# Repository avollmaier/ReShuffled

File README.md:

## Informatik-Konzept
Den informatischen Teil der Arbeit kann man grundsätzlich in 2 Bereiche aufteilen. Es soll
eine einfache grafische Benutzeroberfläche gestaltet werden, auf welcher man den Mischvorgang
steuern sowie grundlegende Einstellungen des Spieles vornehmen kann. Aus programmtechnischen
Gründen wird hierfür die Programmiersprache Java und das GUI-Toolkit Swing verwendet.
Die Hardwarekomponenten setzen sich aus einem Raspberry Pi 3B+ und einem 7"LCD Touchscreen
der Firma Elecrow zusammen.

Zusätzlich besteht dieser Teilbereich der Arbeit auch aus der hardwarenahen Programmierung der
Hauptplatine. Mithilfe der Programmiersprache C sollte der verbaute 8-Bit Mikrocontroller der
AVR-Familie namens ATmega324P programmiert werden. Dieser steuert den gesamten Ablauf
der Maschiene.
Der Datenaustausch zwischen der Hauptplatine und dem Raspberry PI erfolgt über die serielle
Schnittstelle namens UART. Im Hintergrund wird gleichzeitig eine Json Logdatei geschrieben.
## Installation
TODO

# Dokumentation
## Wichtigste Funktionen
### Raspberry

 - Steuerung der gesamten Maschine
 - Grafische Benutzeroberfläche
 - Übertragung der Daten per UART  
 - Auswertung der Daten

### Motherboard
 * Einlesen der Sensordaten  
 * Übertragung der Daten per UART  
 * Auswertung der Daten
 * Steuerung des Motors sowie der Hubmagnete
## Arten von Daten und deren Erfassung
  
 * 3x Kapazitiver Sensor (DIGITAL)

## Protokoll
Das Protokoll ist verbindungslos und Request-Response- (Master-Slave) -orientiert. Die Datenübertragung erfolgt textuell wobei nur Großbuchstaben verwendet werden dürfen, die CRC32-Prüfsumme wird mit einer im Raspberry gespeicherte Tabelle realisiert und nur über die Daten und dem Trennzeichen `#` berechnet. 

### Aufbau:
| Doppelpunkt `:` | Daten (ASCII)| Trennzeichen `#` | CRC32-Prüfsumme | Semicolon `\n` |
| --------------- | ------------------------------------------------ | ----------- | --------------- | ------------- |
| 8-Bit | 16-Bit | 8-Bit | 32-Bit | 8-Bit

### Requests (mit Response-Beispielen)
| Request | Request-String Rx | Response | Response-String Tx |
| ------- | ------------- | -------- | ------------------ |
| INIT | `IN` | Initialisierungs-Zustand | `:OK#CRC;` oder`:E<code>#CRC;` |
| SHUFFLE | `SH` | setzt State "Shuffle" | `:OK#CRC;` oder`:E<code>#CRC;` |
| DEAL | `D<Anzahl der karten>` | setzt State "Deal" | `:OK#CRC;` oder`:E<code>#CRC;` 
| AUTODEAL | `A<Anzahl der karten>` | setzt State "AutoDeal" (standartmäßig 4x5) | `:OK#CRC;` oder`:E<code>#CRC;` |
| SHUTDOWN | `XX` | setzt State "Shutdown" | `:OK#CRC;` oder`:E<code>#CRC;` |

### Requests (mit Response-Beispielen)
Als Response kann entweder `:OK#CRC;` als Zeichen für ein gültiges Verarbeiten des Befehls am Mainboard oder ein `:E<code>#CRC;` zurückgegeben werden.  Dieser Errorcode sagt folgendes aus:

 - `:E<1>#CRC;` -->  TODO
 - `:E<2>#CRC;` -->  TODO
 - `:E<3>#CRC;` -->  TODO

# CommLog-Files
  Im Entwicklunsmodus die gesamte Kommunikation als .json-Datei in das Verzeichnis `/home/pi/ReShuffled_PI/reshuffled.log` gespeichert.
  
  Diese Datei ist so zu lesen:  
### REQUESTS
`Zeitstempel : Name des Requests`
### RESPONSES
`Zeitstempel : Response CRC: *empfangener CRC* <-> *berechneter CRC*`

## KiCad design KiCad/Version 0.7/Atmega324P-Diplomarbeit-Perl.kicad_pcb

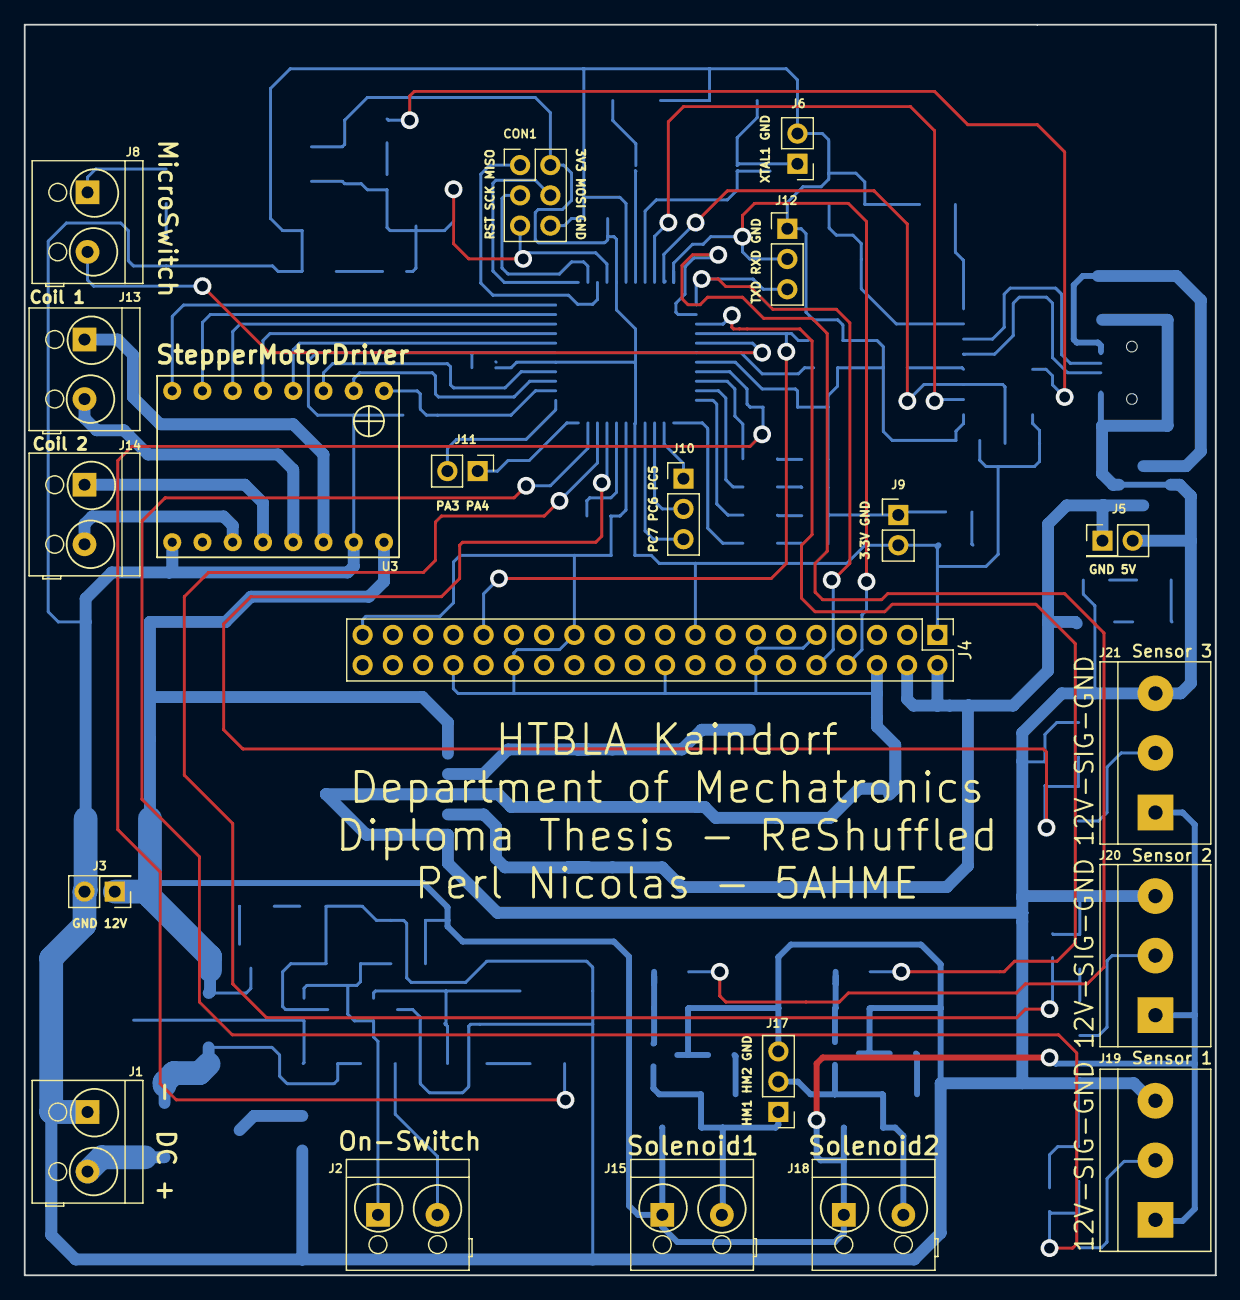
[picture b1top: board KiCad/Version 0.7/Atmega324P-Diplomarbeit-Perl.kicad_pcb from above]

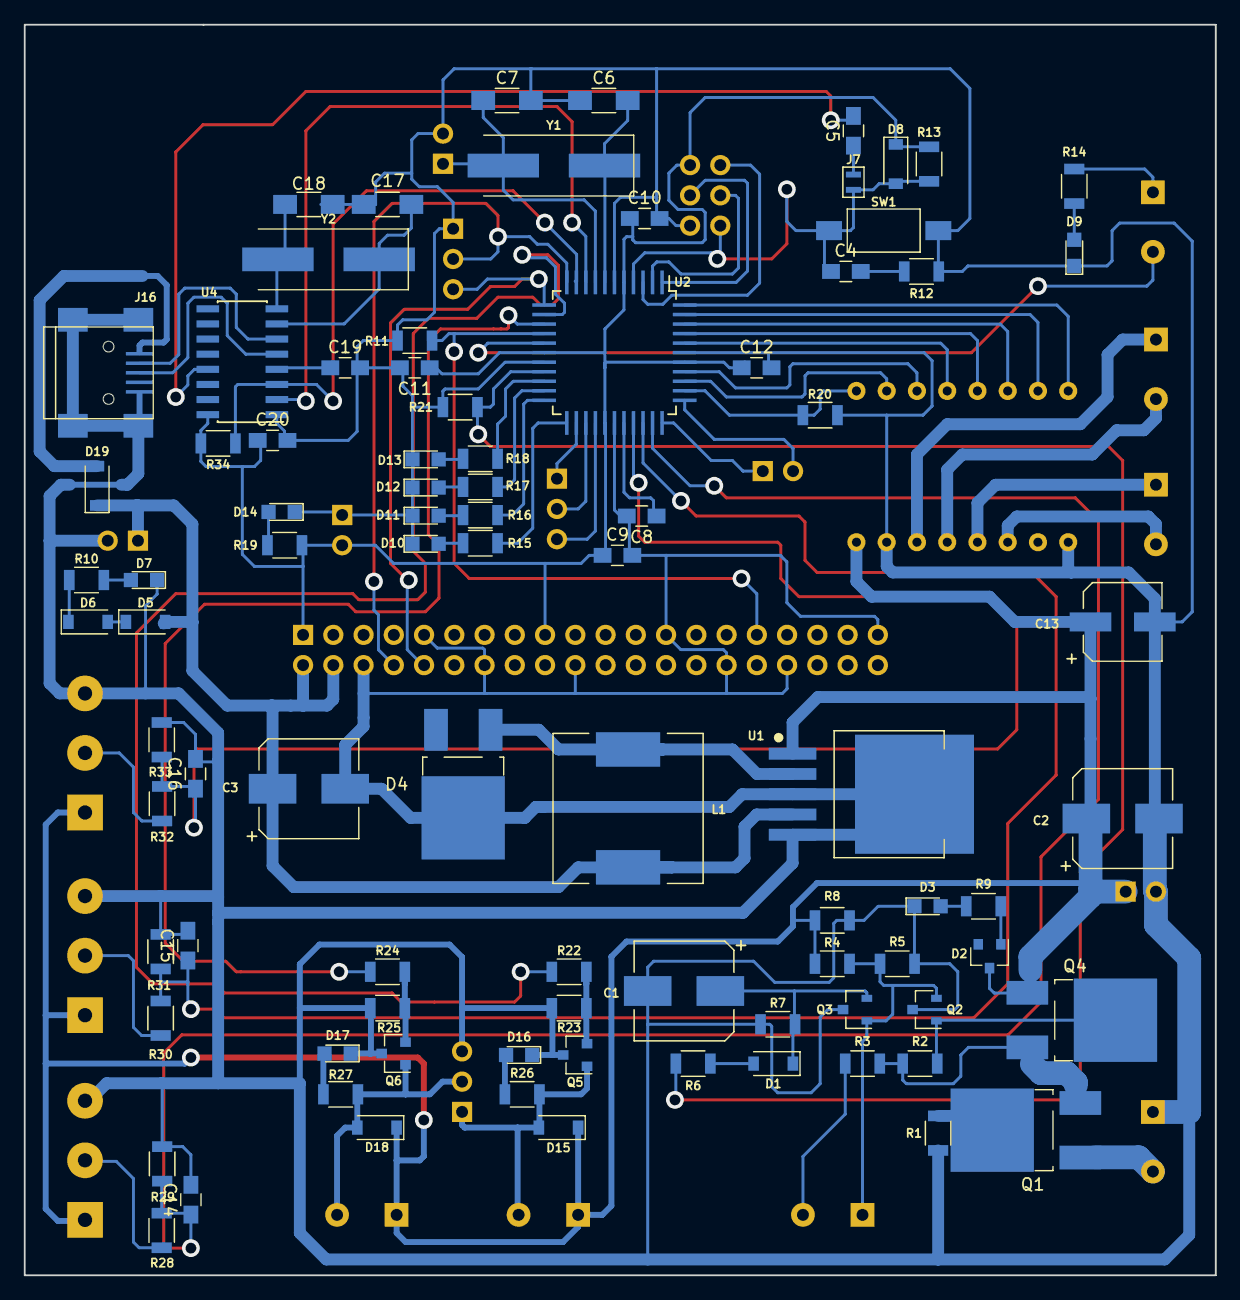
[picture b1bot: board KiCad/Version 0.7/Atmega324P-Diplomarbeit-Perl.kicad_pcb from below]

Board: 2 copper layers, 100.0 x 105.0 mm, 109 parts (88 on the bottom side), 82 nets.

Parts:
C1, C2: 100µ; CP_Elec_8x6.7
C3: 1000µ; CP_Elec_8x6.7
C4, C5, C8, C9, C10, C11, C12, C14, C15, C16, C19, C20: 100n; C_0805_HandSoldering
C6, C7, C17, C18: 22pF; C_1206_HandSoldering
C13: 47µ; CP_Elec_6.3x5.8
CON1: AVR-ISP-6; Pin_Header_Straight_2x03_Pitch2.54mm
D1, D8, D19: MBR130; D_SOD-123
D2: BZX84-C8V2; D_SOT-23_ANK
D3, D7, D9, D10, D11, D12, D13, D14, D16, D17: LED; LED_0805
D4: MBRD340; TO-252-2_Rectifier
D5, D6, D15, D18: RR264M; D_SOD-123
J1: Input_12V; Terminalblock-2x-5mm
J2: PowerOn_Button; Terminalblock-2x-5mm
J3, J5: Conn_01x02; Pin_Header_Straight_2x01_Pitch2.54mm
J4: Raspberry_Pi_3B+; Pin_Header_Straight_2x20_Pitch2.54mm
J6, J9, J11: Conn_01x02; Pin_Header_Straight_1x02_Pitch2.54mm
J7: GS2
J8: Microswitch; Terminalblock-2x-5mm
J10, J12, J17: Conn_01x03; Pin_Header_Straight_1x03_Pitch2.54mm
J13: Stepper1; Terminalblock-2x-5mm
J14: Stepper2; Terminalblock-2x-5mm
J15: Solenoid1; Terminalblock-2x-5mm
J16: USB_OTG; USB_Mini-B
J18: Solenoid2; Terminalblock-2x-5mm
J19: Cap_Sensor1; Terminalblock-3x-5mm
J20: Cap_Sensor2; Terminalblock-3x-5mm
J21: Cap_Sensor3; Terminalblock-3x-5mm
L1: 100µ; L_12x12mm_h6mm
Q1, Q4: FDD6637; TO-252-2_Rectifier
Q2, Q3, Q5, Q6: FDN337N; SOT-23
R1, R8, R11, R13, R20, R21, R34: 47k; R_1206
R2, R3, R4, R5, R23, R25: 10k; R_1206
R6, R9, R10, R12, R14, R15, R16, R17, R18, R19, R22, R24, R26, R27: 560; R_1206
R7: 100k; R_1206
R28, R30, R32: 5.6k; R_1206
R29, R31, R33: 4.7k; R_1206
SW1: SW_Push; SW_SPST_FSMSM
U1: LM2576-5.0WU; DPAK6P170_1524X459L254X81N
U2: ATMEGA324P-20AU; TQFP-44_10x10mm_Pitch0.8mm_Handsolded
U3: StepperMotorDriver; StepperSocket
U4: CH340G; SOIC-16_3.9x9.9mm_Pitch1.27mm_HANDSOLDERED
Y1: Crystal_10Mhz; Crystal_SMD_HC49-SD
Y2: Crystal_12Mhz; Crystal_SMD_HC49-SD

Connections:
12V: C2.1, C13.1, D2.1, D15.1, D18.1, J3.1, J15.1, J18.1, J19.1, J20.1, J21.1, Q4.1, R4.2, R8.1, U1.1, U3.9
+3V3: C9.1, C10.1, C11.1, C12.1, C20.1, CON1.2, D8.1, J4.1, J4.17, J9.2, R13.1, R19.1, R34.1, U2.5, U2.17, U2.27, U2.38, U4.16
+5V: C3.1, D5.2, D19.1, J4.2, J4.4, J5.1, L1.2, U1.4
/Peripherie/WATCHDOG: J4.31, R11.1, U2.15
/Peripherie/µC_RxD: J4.8, J12.2, U2.11
/Peripherie/µC_TxD: J4.10, J12.3, U2.12
DIR: U2.44, U3.8
DTR_USB: C5.2, U4.13
EN: R20.1, U2.35, U3.1
GND: C1.2, C2.2, C3.2, C6.2, C7.2, C8.2, C9.2, C10.2, C11.2, C12.2, C13.2, C14.2, C15.2, C16.2, C17.2, C18.2, C19.2, C20.2, CON1.6, D3.1, D4.2, D7.1, D9.1, D10.1, D11.1, D12.1, D13.1, D14.1, D16.1, D17.1, J1.1, J3.2, J4.6, J4.9, J4.14, J4.20, J4.25, J4.30, J4.34, J4.39, J5.2, J6.2, J9.1, J12.1, J16.5, J16.6, J17.3, J19.3, J20.3, J21.3, Q2.3, Q3.3, Q5.3, Q6.3, R1.1, R5.2, R7.2, R8.2, R11.2, R12.1, R20.2, R21.2, R23.2, R25.2, R29.2, R31.2, R33.2, SW1.1, U1.3, U1.5, U1.6, U2.6, U2.18, U2.28, U2.39, U3.10, U3.16, U4.1
HM1: R22.2, U2.13
HM2: R24.2, U2.14
LED1: R18.2, U2.20
LED2: R17.2, U2.21
LED3: R16.2, U2.22
LED4: R15.2, U2.23
M0: U2.36, U3.2
M1: U2.37, U3.3
M2: U2.40, U3.4
MISO: CON1.1, U2.3
MOSI: CON1.4, U2.1
MSWITCH: J8.2, U2.16
unnamed: C1.1, D1.1, Q3.2, R7.1
unnamed: C4.2, R12.2
unnamed: C5.1, J7.2
unnamed: C6.1, U2.7, Y1.1
unnamed: C7.1, J6.1, U2.8, Y1.2
unnamed: C8.1, U2.29
unnamed: C17.1, U4.7, Y2.1
unnamed: C18.1, U4.8, Y2.2
unnamed: C19.1, U4.4
unnamed: D1.2, R6.1
unnamed: D2.2, R9.1
unnamed: D3.2, R9.2
unnamed: D4.1, L1.1, U1.2
unnamed: D5.1, D6.2
unnamed: D6.1, R10.1
unnamed: D7.2, R10.2
unnamed: D9.2, R14.1
unnamed: D10.2, R15.1
unnamed: D11.2, R16.1
unnamed: D12.2, R17.1
unnamed: D13.2, R18.1
unnamed: D14.2, R19.2
unnamed: D15.2, J15.2, J17.1, Q5.1, R26.2
unnamed: D16.2, R26.1
unnamed: D17.2, R27.1
unnamed: D18.2, J17.2, J18.2, Q6.1, R27.2
unnamed: D19.2, J16.1
unnamed: J1.2, Q1.1
unnamed: J2.1, Q2.2, Q3.1, R4.1, R5.1
unnamed: J2.2, R3.2
unnamed: J8.1, R14.2
unnamed: J10.1, U2.24
unnamed: J10.2, U2.25
unnamed: J10.3, U2.26
unnamed: J11.1, U2.33
unnamed: J11.2, U2.34
unnamed: J13.1, U3.11
unnamed: J13.2, U3.12
unnamed: J14.1, U3.13
unnamed: J16.2, U4.6
unnamed: J16.3, U4.5
unnamed: J19.2, R28.1
unnamed: J20.2, R30.1
unnamed: J21.2, R32.1
unnamed: Q1.2, R1.2
unnamed: Q1.3, Q4.3, R2.1, R3.1
unnamed: Q2.1, Q4.2, R2.2
unnamed: Q5.2, R22.1, R23.1
unnamed: Q6.2, R24.1, R25.1
RESET_M: U2.41, U3.5
RST: C4.1, CON1.5, D8.2, J7.1, R13.2, SW1.2, U2.4
RxD_USB: R34.2, U2.10, U4.3
S1: C14.1, R28.2, R29.1, U2.32
S2: C15.1, R30.2, R31.1, U2.31
S3: C16.1, R32.2, R33.1, U2.30
SCK: CON1.3, U2.2
SLEEP: U2.42, U3.6
STEP: U2.43, U3.7
TxD_USB: U2.9, U4.2
UNLATCH: R6.2, R21.1, U2.19

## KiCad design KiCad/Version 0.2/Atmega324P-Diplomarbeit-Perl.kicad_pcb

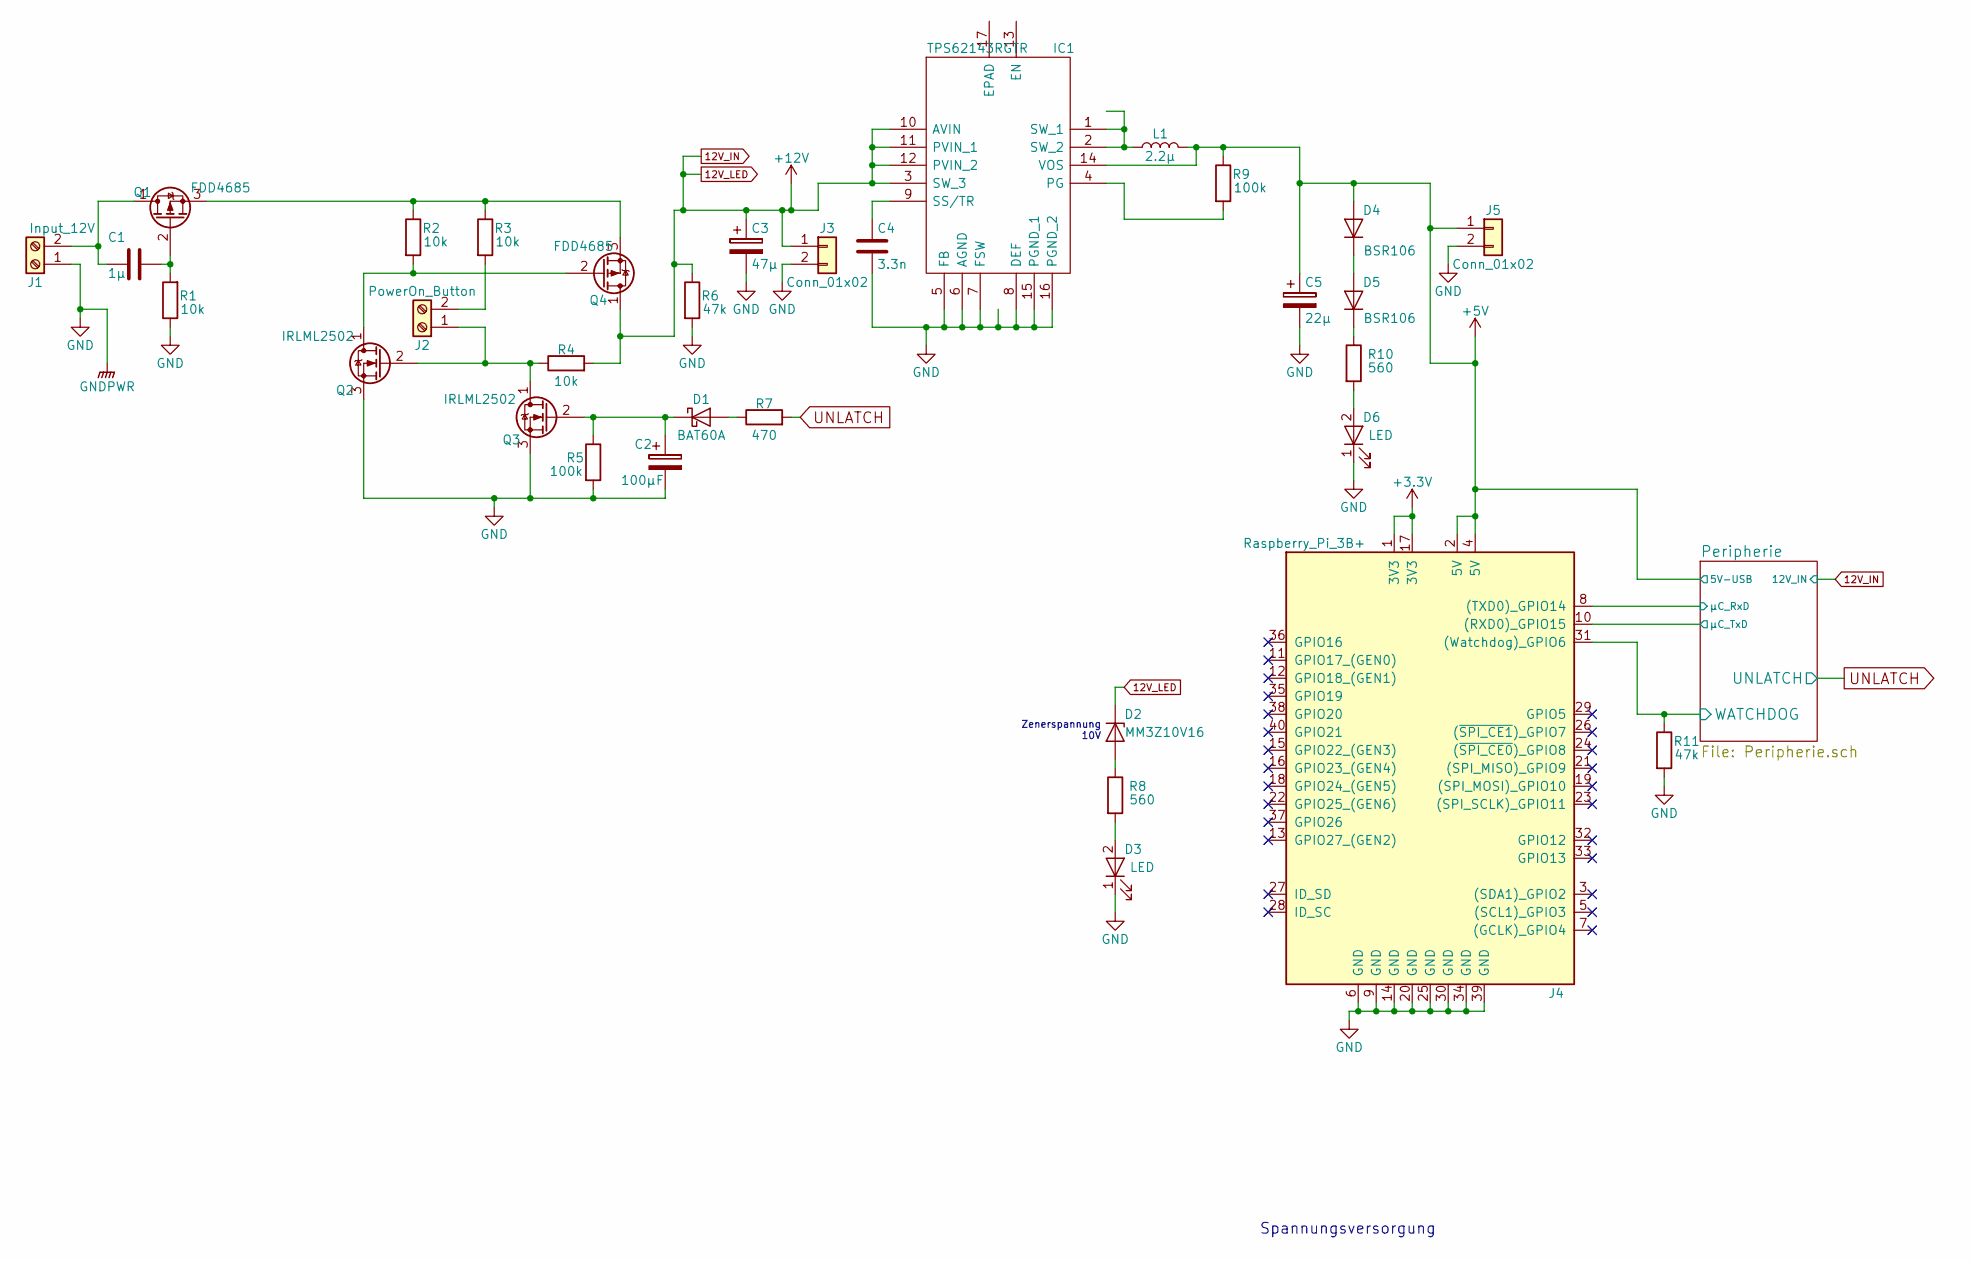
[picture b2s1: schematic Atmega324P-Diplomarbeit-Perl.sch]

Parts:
C1: 1µ; CP_Elec_4x5.3
C2: 100µF; CP_Elec_6.3x7.7
C3: 47µ; CP_Elec_6.3x7.7
C4: 3.3n; C_1206_HandSoldering
C5: 22µ; CP_Elec_6.3x7.7
D1: BAT60A; D_SOD-323
D2: MM3Z10V16; D_SOD-323
D3, D6: LED; D_0805
D4, D5: BSR106; D_SOD-323
IC1: TPS62143RGTR; QFN50P300X300X100-17N-D; Mouser Part Number 595-TPS62143RGTR
J1: Input_12V; Terminalblock-2x-5mm
J2: PowerOn_Button; Terminalblock-2x-5mm
J3, J5: Conn_01x02; Pin_Header_Straight_2x01_Pitch2.54mm
J4: Raspberry_Pi_3B+; Pin_Header_Straight_2x20
L1: 2.2µ; L_Wuerth_MAPI-4020
Q1, Q4: FDD4685; TO-252-3_TabPin2
Q2, Q3: IRLML2502; SOT-23
R1, R2, R3, R4: 10k; R_1206
R5, R9: 100k; R_1206
R6, R11: 47k; R_1206
R7: 470; R_1206
R8, R10: 560; R_1206

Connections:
+3V3: J4.1 (3V3), J4.17 (3V3); also elsewhere on the board
+5V: C5.1, D4.2 (A), IC1.14 (VOS), J4.2 (5V), J4.4 (5V), J5.1, L1.2, R9.1; also elsewhere on the board
/Peripherie/WATCHDOG: J4.31 ((Watchdog)_GPIO6), R11.1; also elsewhere on the board
/Peripherie/µC_RxD: J4.8 ((TXD0)_GPIO14); also elsewhere on the board
/Peripherie/µC_TxD: J4.10 ((RXD0)_GPIO15); also elsewhere on the board
GND: C2.2, C3.2, C4.2, C5.2, D3.1 (K), D6.1 (K), IC1.5 (FB), IC1.6 (AGND), IC1.7 (FSW), IC1.8 (DEF), IC1.15 (PGND_1), IC1.16 (PGND_2), IC1.17 (EPAD), J1.1, J3.2, J4.6 (GND), J4.9 (GND), J4.14 (GND), J4.20 (GND), J4.25 (GND), J4.30 (GND), J4.34 (GND), J4.39 (GND), J5.2, Q2.3 (S), Q3.3 (S), R1.1, R5.2, R6.2, R11.2; also elsewhere on the board
unnamed: C1.1, Q1.2 (G), R1.2
unnamed: C1.2, J1.2, Q1.1 (D)
unnamed: C2.1, D1.1 (K), Q3.2 (G), R5.1
unnamed: C4.1, IC1.9 (SS/TR)
unnamed: D1.2 (A), R7.1
unnamed: D2.2 (A), R8.1
unnamed: D3.2 (A), R8.2
unnamed: D4.1 (K), D5.2 (A)
unnamed: D5.1 (K), R10.1
unnamed: D6.2 (A), R10.2
unnamed: IC1.4 (PG), R9.2
unnamed: J2.1, Q2.2 (G), Q3.1 (D), R4.1
unnamed: J2.2, R3.2
unnamed: Q1.3 (S), Q4.3 (S), R2.1, R3.1
unnamed: Q2.1 (D), Q4.2 (G), R2.2
UNLATCH: R7.2; also elsewhere on the board

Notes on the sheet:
Spannungsversorgung
Zenerspannung 10V

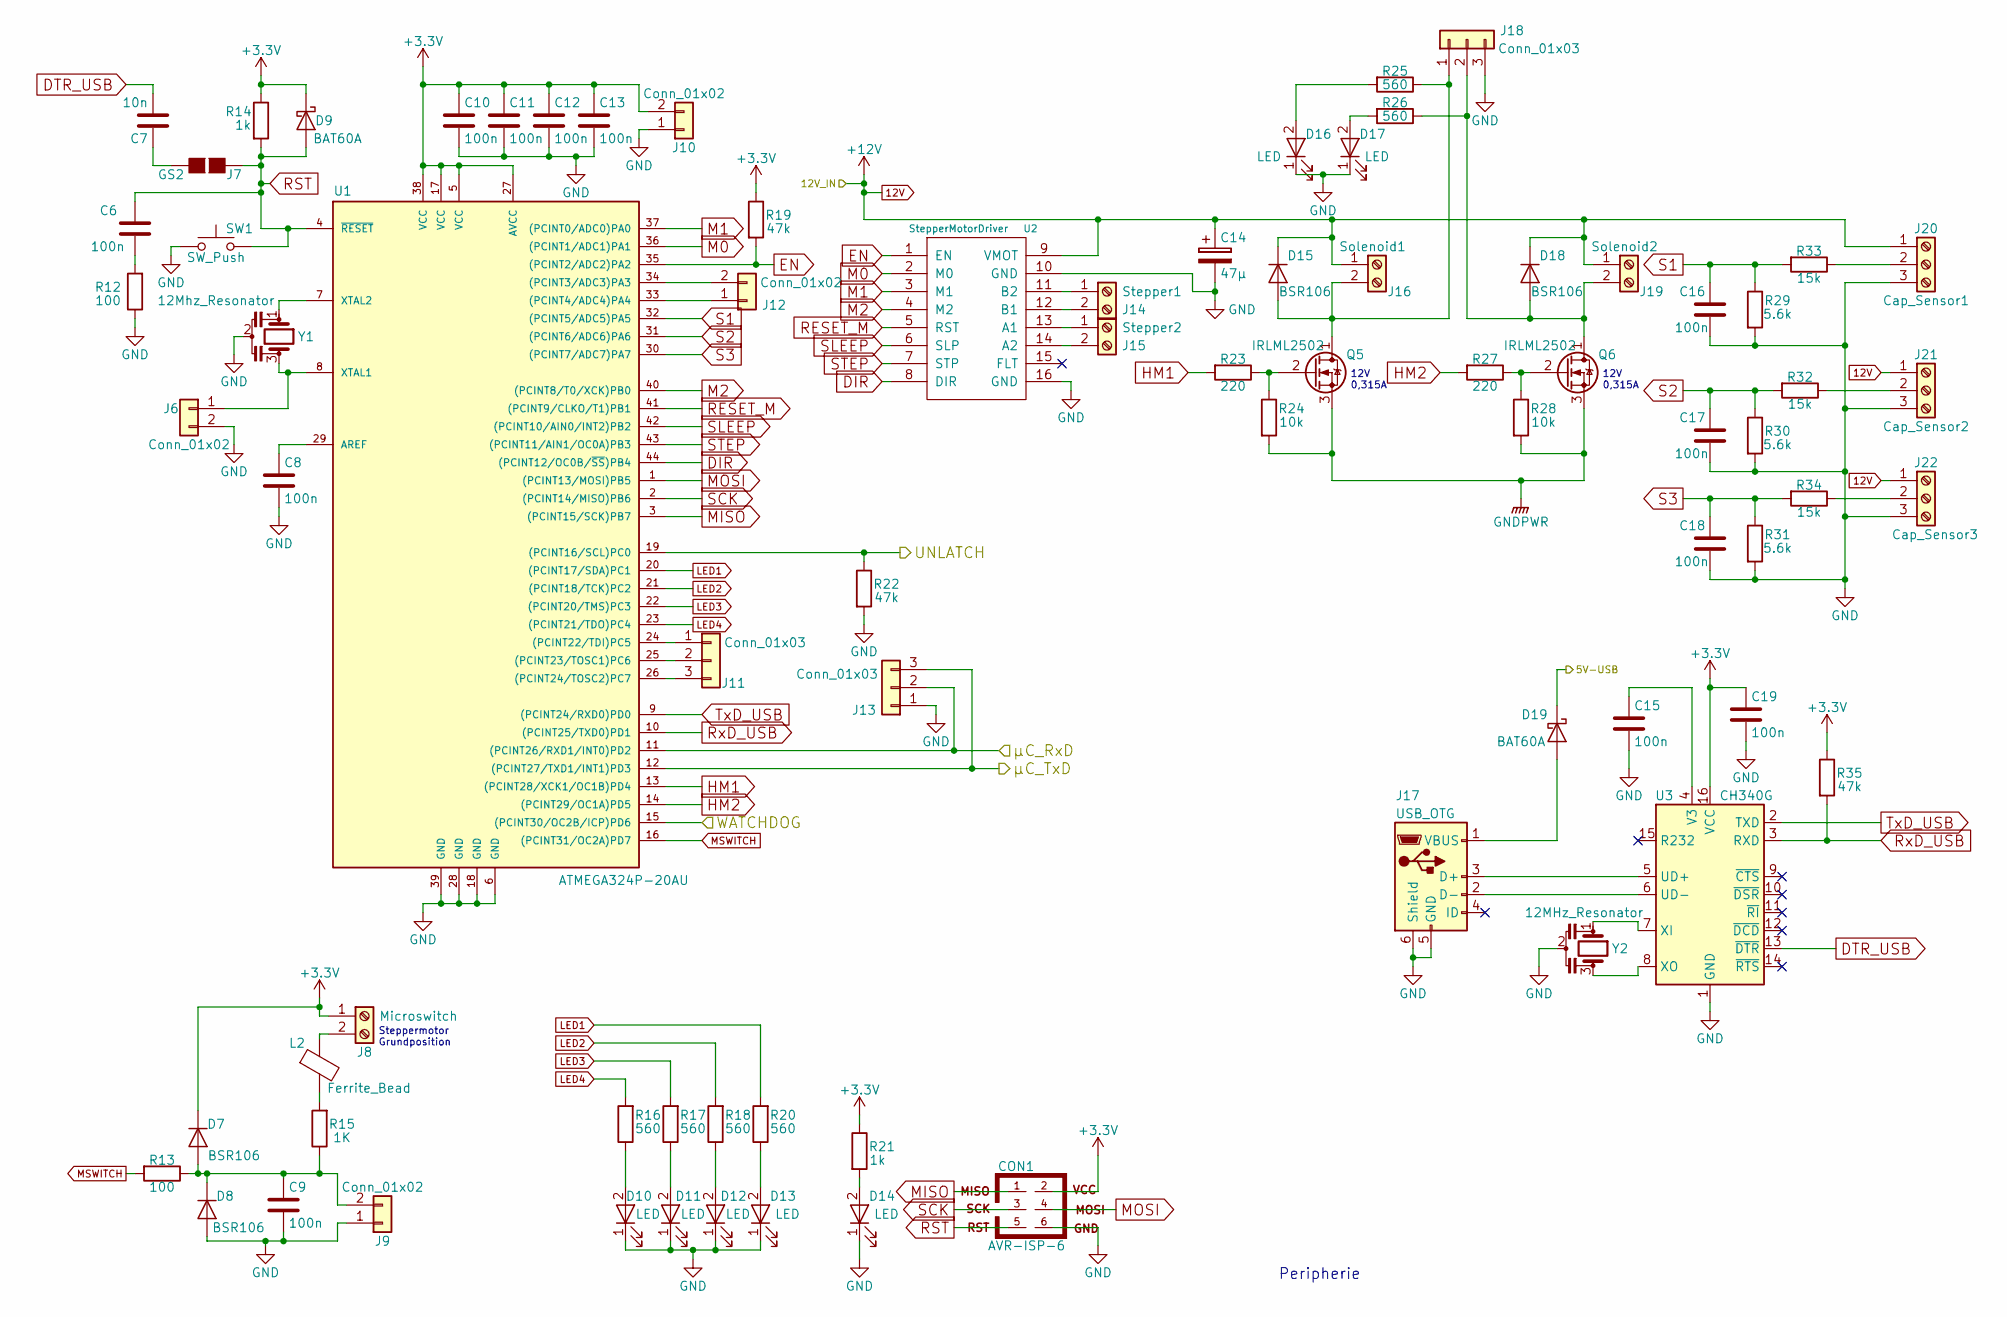
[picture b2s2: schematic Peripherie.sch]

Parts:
C6, C8, C9, C10, C11, C12, C13, C15, C16, C17, C18, C19: 100n; C_1206_HandSoldering
C7: 10n; C_1206_HandSoldering
C14: 47µ; CP_Elec_6.3x7.7
CON1: AVR-ISP-6; Pin_Header_Straight_2x03_Pitch2.54mm
D7, D8, D15, D18: BSR106; D_SOD-323
D9, D19: BAT60A; D_SOD-323
D10, D11, D12, D13, D14, D16, D17: LED; D_0805
J6, J9, J10, J12: Conn_01x02; Pin_Header_Straight_1x02_Pitch2.54mm
J7: GS2
J8: Microswitch; Terminalblock-2x-5mm
J11, J13, J18: Conn_01x03; Pin_Header_Straight_1x03_Pitch2.54mm
J14: Stepper1; Terminalblock-2x-5mm
J15: Stepper2; Terminalblock-2x-5mm
J16: Solenoid1; Terminalblock-2x-5mm
J17: USB_OTG; USB_Mini-B-THT
J19: Solenoid2; Terminalblock-2x-5mm
J20: Cap_Sensor1; Terminalblock-3x-5mm
J21: Cap_Sensor2; Terminalblock-3x-5mm
J22: Cap_Sensor3; Terminalblock-3x-5mm
L2: Ferrite_Bead; L_0805_HandSoldering
Q5, Q6: IRLML2502; SOT-23
R12, R13: 100; R_1206
R14, R21: 1k; R_1206
R15: 1K; R_1206
R16, R17, R18, R20, R25, R26: 560; R_1206
R19, R22, R35: 47k; R_1206
R23, R27: 220; R_1206
R24, R28: 10k; R_1206
R29, R30, R31: 5.6k; R_1206
R32, R33, R34: 15k; R_1206
SW1: SW_Push; SW_SPST_FSMSM
U1: ATMEGA324P-20AU; TQFP-44_10x10mm_Pitch0.8mm_Handsolded
U2: StepperMotorDriver; StepperSocket
U3: CH340G; SOIC-16_3.9x9.9mm_Pitch1.27mm_HANDSOLDERED
Y1: 12Mhz_Resonator; Resonator-3pin_w7.0mm_h2.5mm
Y2: 12MHz_Resonator; Resonator-3pin_w7.0mm_h2.5mm

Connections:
+3V3: C10.1, C11.1, C12.1, C13.1, C19.1, CON1.2, D7.1 (K), D9.1 (K), J8.1, J10.2, R14.1, R19.1, R21.1, R35.1, U1.5 (VCC), U1.17 (VCC), U1.27 (AVCC), U1.38 (VCC), U3.16 (VCC); also elsewhere on the board
+5V: D19.1 (K); also elsewhere on the board
/Peripherie/WATCHDOG: U1.15 ((PCINT30/OC2B/ICP)PD6); also elsewhere on the board
/Peripherie/µC_RxD: J13.2, U1.11 ((PCINT26/RXD1/INT0)PD2); also elsewhere on the board
/Peripherie/µC_TxD: J13.3, U1.12 ((PCINT27/TXD1/INT1)PD3); also elsewhere on the board
DIR: U1.44 ((PCINT12/OC0B/~SS~)PB4), U2.8 (DIR)
DTR_USB: C7.2, U3.13 (~DTR)
EN: R19.2, U1.35 ((PCINT2/ADC2)PA2), U2.1 (EN)
GND: C8.2, C9.2, C10.2, C11.2, C12.2, C13.2, C14.2, C15.2, C16.2, C17.2, C18.2, C19.2, CON1.6, D8.2 (A), D10.1 (K), D11.1 (K), D12.1 (K), D13.1 (K), D14.1 (K), D16.1 (K), D17.1 (K), J6.2, J9.1, J10.1, J13.1, J17.5 (GND), J17.6 (Shield), J18.3, J20.3, J21.3, J22.3, Q5.3 (S), Q6.3 (S), R12.1, R22.2, R24.2, R28.2, R29.2, R30.2, R31.2, SW1.1, U1.6 (GND), U1.18 (GND), U1.28 (GND), U1.39 (GND), U2.10 (GND), U2.16 (GND), U3.1 (GND), Y1.2, Y2.2; also elsewhere on the board
HM1: R23.2, U1.13 ((PCINT28/XCK1/OC1B)PD4)
HM2: R27.2, U1.14 ((PCINT29/OC1A)PD5)
LED1: R20.2, U1.20 ((PCINT17/SDA)PC1)
LED2: R18.2, U1.21 ((PCINT18/TCK)PC2)
LED3: R17.2, U1.22 ((PCINT20/TMS)PC3)
LED4: R16.2, U1.23 ((PCINT21/TDO)PC4)
M0: U1.36 ((PCINT1/ADC1)PA1), U2.2 (M0)
M1: U1.37 ((PCINT0/ADC0)PA0), U2.3 (M1)
M2: U1.40 ((PCINT8/T0/XCK)PB0), U2.4 (M2)
MISO: CON1.1, U1.3 ((PCINT15/SCK)PB7)
MOSI: CON1.4, U1.1 ((PCINT13/MOSI)PB5)
MSWITCH: R13.2, U1.16 ((PCINT31/OC2A)PD7)
unnamed: C6.2, R12.2
unnamed: C7.1, J7.2 (G2)
unnamed: C8.1, U1.29 (AREF)
unnamed: C9.1, D7.2 (A), D8.1 (K), J9.2, R13.1, R15.1
unnamed: C15.1, U3.4 (V3)
unnamed: D10.2 (A), R16.1
unnamed: D11.2 (A), R17.1
unnamed: D12.2 (A), R18.1
unnamed: D13.2 (A), R20.1
unnamed: D14.2 (A), R21.2
unnamed: D15.2 (A), J16.2, J18.1, Q5.1 (D), R25.1
unnamed: D16.2 (A), R25.2
unnamed: D17.2 (A), R26.2
unnamed: D18.2 (A), J18.2, J19.2, Q6.1 (D), R26.1
unnamed: D19.2 (A), J17.1 (VBUS)
unnamed: J6.1, U1.8 (XTAL1), Y1.3
unnamed: J8.2, L2.1
unnamed: J11.1, U1.24 ((PCINT22/TDI)PC5)
unnamed: J11.2, U1.25 ((PCINT23/TOSC1)PC6)
unnamed: J11.3, U1.26 ((PCINT24/TOSC2)PC7)
unnamed: J12.1, U1.33 ((PCINT4/ADC4)PA4)
unnamed: J12.2, U1.34 ((PCINT3/ADC3)PA3)
unnamed: J14.1, U2.11 (B2)
unnamed: J14.2, U2.12 (B1)
unnamed: J15.1, U2.13 (A1)
unnamed: J15.2, U2.14 (A2)
unnamed: J17.2 (D-), U3.6 (UD-)
unnamed: J17.3 (D+), U3.5 (UD+)
unnamed: J20.2, R33.1
unnamed: J21.2, R32.1
unnamed: J22.2, R34.1
unnamed: L2.2, R15.2
unnamed: Q5.2 (G), R23.1, R24.1
unnamed: Q6.2 (G), R27.1, R28.1
unnamed: U1.7 (XTAL2), Y1.1
unnamed: U3.7 (XI), Y2.1
unnamed: U3.8 (XO), Y2.3
RESET_M: U1.41 ((PCINT9/CLKO/T1)PB1), U2.5 (RST)
RST: C6.1, CON1.5, D9.2 (A), J7.1 (G1), R14.2, SW1.2, U1.4 (~RESET)
RxD_USB: R35.2, U1.10 ((PCINT25/TXD0)PD1), U3.3 (RXD)
S1: C16.1, R29.1, R33.2, U1.32 ((PCINT5/ADC5)PA5)
S2: C17.1, R30.1, R32.2, U1.31 ((PCINT6/ADC6)PA6)
S3: C18.1, R31.1, R34.2, U1.30 ((PCINT7/ADC7)PA7)
SCK: CON1.3, U1.2 ((PCINT14/MISO)PB6)
SLEEP: U1.42 ((PCINT10/AIN0/INT2)PB2), U2.6 (SLP)
STEP: U1.43 ((PCINT11/AIN1/OC0A)PB3), U2.7 (STP)
TxD_USB: U1.9 ((PCINT24/RXD0)PD0), U3.2 (TXD)
UNLATCH: R22.1, U1.19 ((PCINT16/SCL)PC0); also elsewhere on the board

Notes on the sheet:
Peripherie
12V 0,315A
Steppermotor Grundposition

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
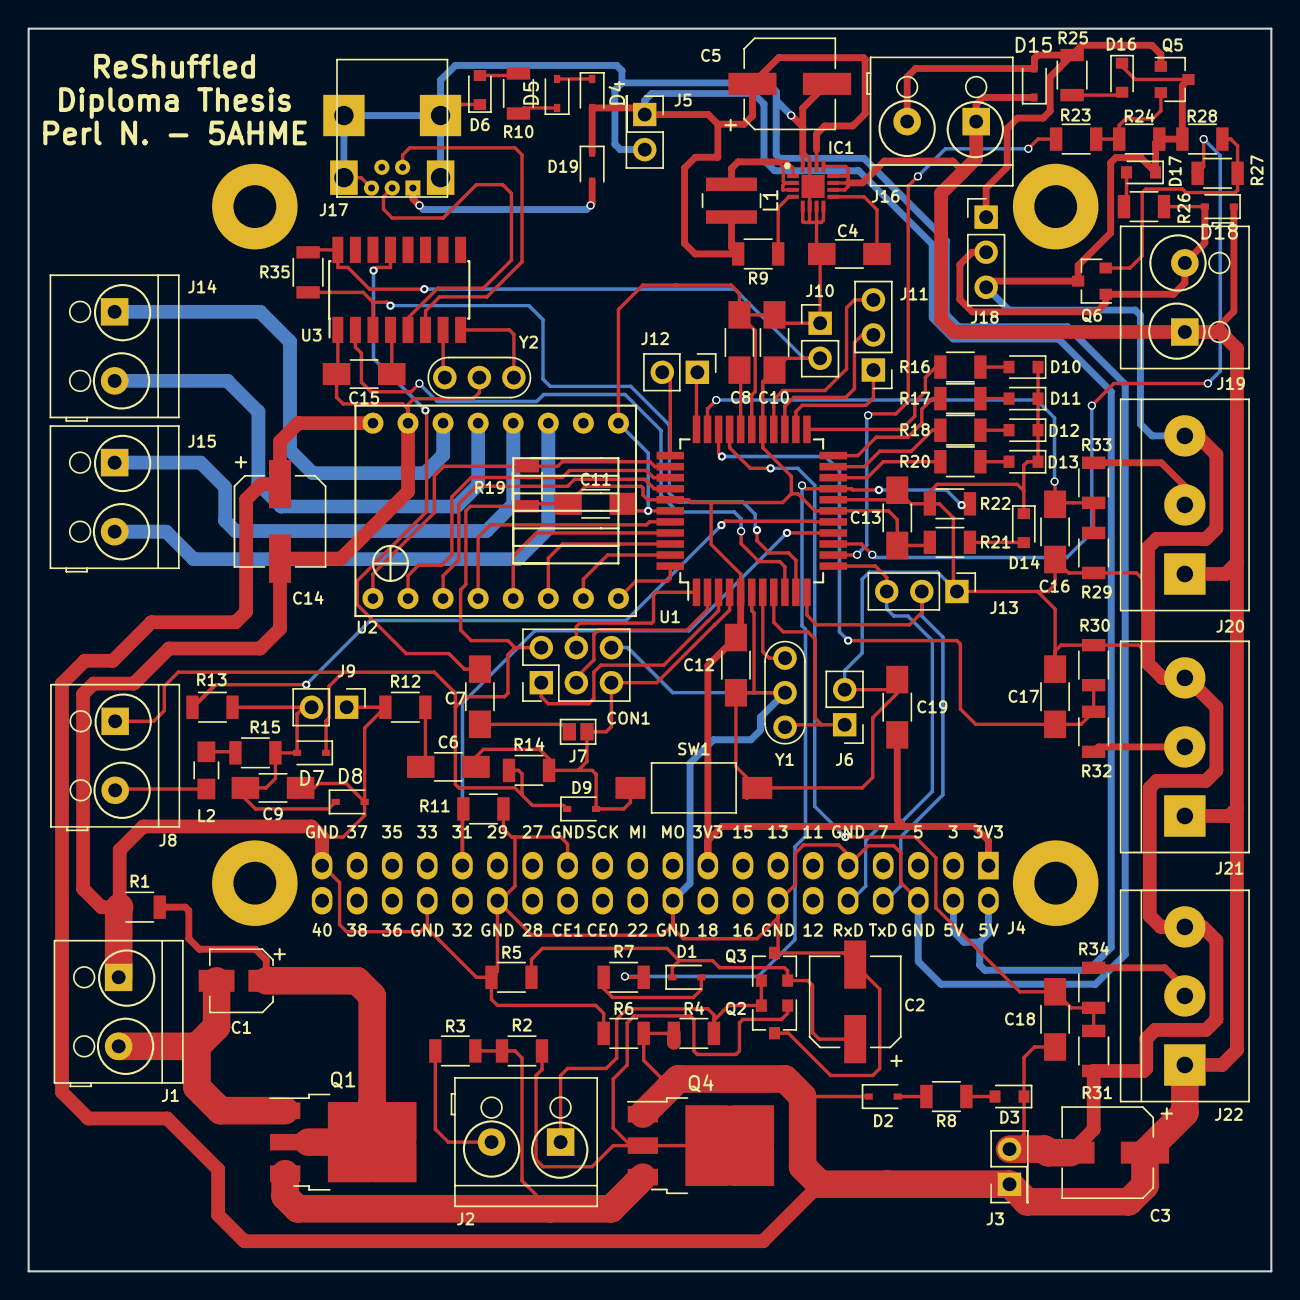
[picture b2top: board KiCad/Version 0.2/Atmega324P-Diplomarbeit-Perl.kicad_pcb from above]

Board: 2 copper layers, 90.0 x 90.0 mm, 111 parts (0 on the bottom side), 86 nets.

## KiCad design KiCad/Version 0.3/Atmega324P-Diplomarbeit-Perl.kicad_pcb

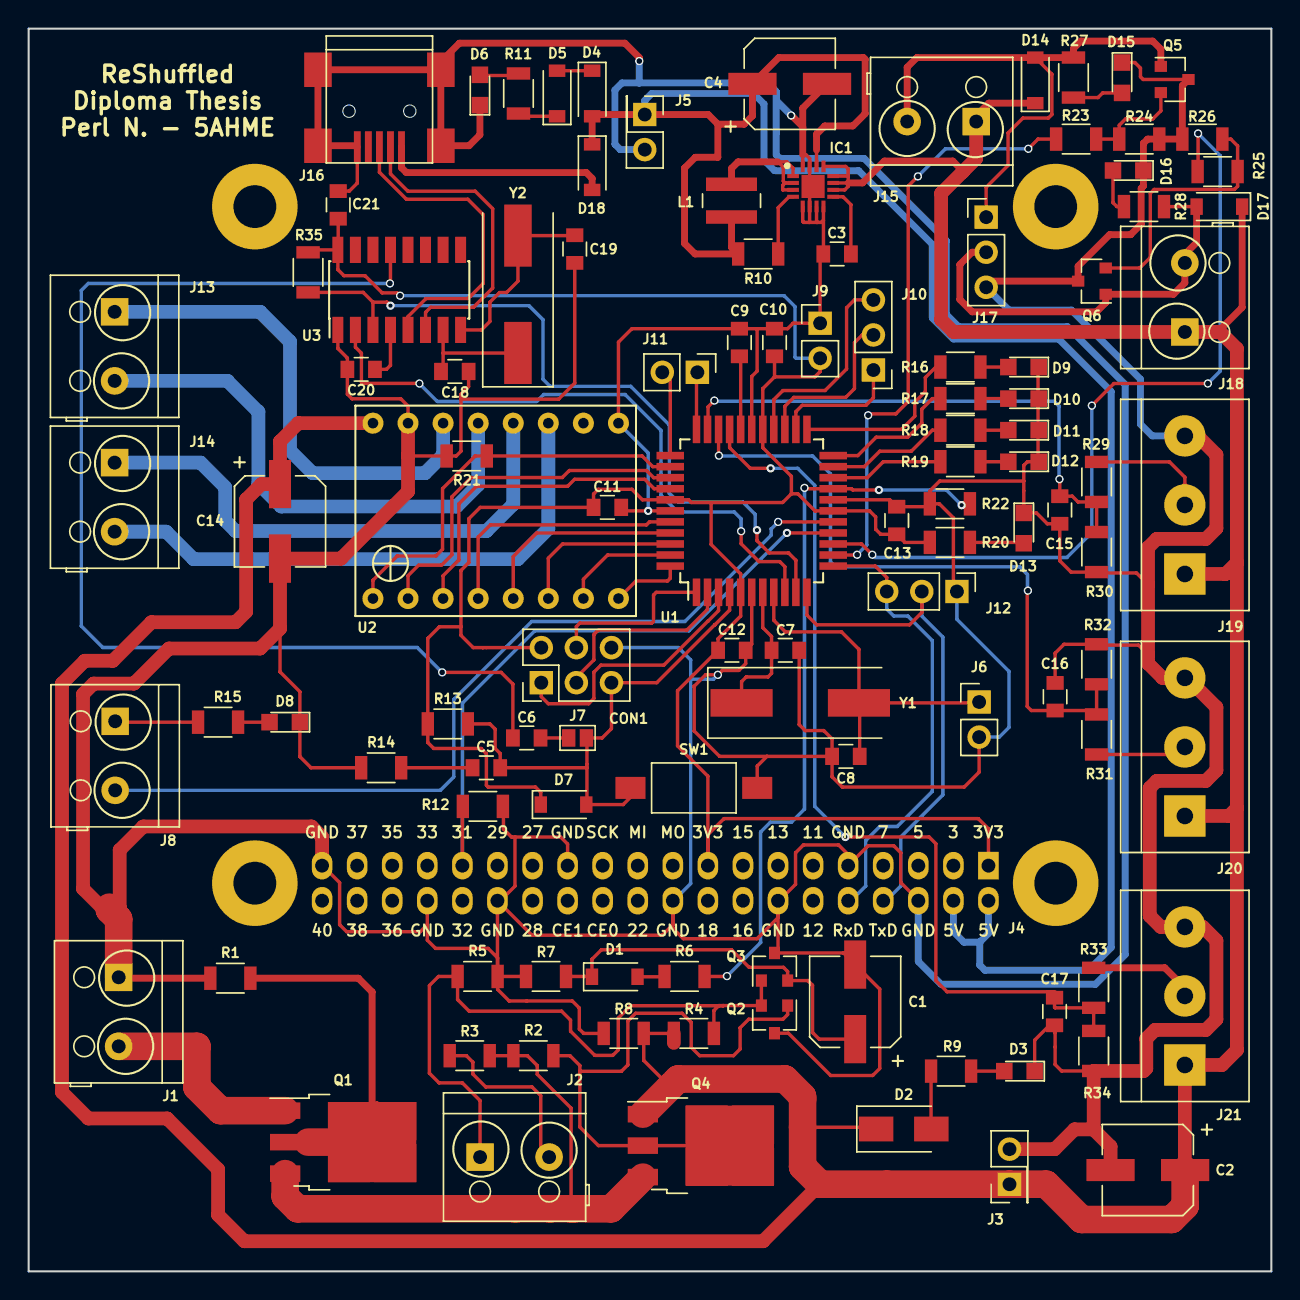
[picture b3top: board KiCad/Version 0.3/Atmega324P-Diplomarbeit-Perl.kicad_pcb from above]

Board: 2 copper layers, 90.0 x 90.0 mm, 110 parts (0 on the bottom side), 85 nets.

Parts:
C1: 100µF; CP_Elec_6.3x5.8
C2, C4, C14: 47µ; CP_Elec_6.3x5.8
C3: 3.3n; C_0805
C5, C9, C10, C11, C12, C13, C15, C16, C17, C20, C21: 100n; C_0805
C6: 10n; C_0805
C7, C8, C18, C19: 22pF; C_0805
CON1: AVR-ISP-6; Pin_Header_Straight_2x03_Pitch2.54mm
D1, D7, D18: MBR130; D_SOD-123
D2: SML4738; D_SMA
D3, D6, D8, D9, D10, D11, D12, D13, D15, D16: LED; LED_0805
D4, D5, D14, D17: RR264M; D_SOD-123
IC1: TPS62143RGTR; QFN50P300X300X100-17N-D
J1: Input_12V; Terminalblock-2x-5mm
J2: PowerOn_Button; Terminalblock-2x-5mm
J3, J5: Conn_01x02; Pin_Header_Straight_2x01_Pitch2.54mm
J4: Raspberry_Pi_3B+; Raspberry-PI
J6, J9, J11: Conn_01x02; Pin_Header_Straight_1x02_Pitch2.54mm
J7: GS2
J8: Microswitch; Terminalblock-2x-5mm
J10, J12, J17: Conn_01x03; Pin_Header_Straight_1x03_Pitch2.54mm
J13: Stepper1; Terminalblock-2x-5mm
J14: Stepper2; Terminalblock-2x-5mm
J15: Solenoid1; Terminalblock-2x-5mm
J16: USB_OTG; USB_Mini-B
J18: Solenoid2; Terminalblock-2x-5mm
J19: Cap_Sensor1; Terminalblock-3x-5mm
J20: Cap_Sensor2; Terminalblock-3x-5mm
J21: Cap_Sensor3; Terminalblock-3x-5mm
L1: 2.2µ; L_Wuerth_MAPI-4020
Q1, Q4: FDD6637; TO-252-3_TabPin2
Q2, Q3, Q5, Q6: FDN337N; SOT-23
R1, R8, R12, R21, R22, R35: 47k; R_1206
R2, R3, R4, R5, R24, R26: 10k; R_1206
R6, R9, R11, R15, R16, R17, R18, R19, R23, R25, R27, R28: 560; R_1206
R7, R10: 100k; R_1206
R13, R20: 1k; R_1206
R14: 100; R_1206
R29, R31, R33: 5.1k; R_1206
R30, R32, R34: 2k; R_1206
SW1: SW_Push; SW_SPST_FSMSM
U1: ATMEGA324P-20AU; TQFP-44_10x10mm_Pitch0.8mm_Handsolded
U2: StepperMotorDriver; StepperSocket
U3: CH340G; SOIC-16_3.9x9.9mm_Pitch1.27mm_HANDSOLDERED
Y1, Y2: Crystal_12Mhz; Crystal_SMD_HC49-SD

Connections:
12V: C2.1, C14.1, D2.1, D14.1, D17.1, IC1.10, IC1.11, IC1.12, IC1.13, J3.1, J15.1, J18.1, J19.1, J20.1, J21.1, Q4.1, R4.2, R8.1, U2.9
+3V3: C10.1, C11.1, C12.1, C13.1, C21.1, CON1.2, D7.1, J4.1, J4.17, J9.2, R13.1, R20.1, R35.1, U1.5, U1.17, U1.27, U1.38, U3.16
+5V: C4.1, D4.2, D18.1, IC1.14, J4.2, J4.4, J5.1, L1.2, R10.1
/Peripherie/WATCHDOG: J4.31, R12.1, U1.15
/Peripherie/µC_RxD: J4.8, J12.2, U1.11
/Peripherie/µC_TxD: J4.10, J12.3, U1.12
DIR: U1.44, U2.8
DTR_USB: C6.2, U3.13
EN: R21.1, U1.35, U2.1
GND: C1.2, C2.2, C3.2, C4.2, C7.2, C8.2, C9.2, C10.2, C11.2, C12.2, C13.2, C14.2, C15.2, C16.2, C17.2, C18.2, C19.2, C20.2, C21.2, CON1.6, D3.1, D6.1, D8.1, D9.1, D10.1, D11.1, D12.1, D13.1, D15.1, D16.1, IC1.5, IC1.6, IC1.7, IC1.8, IC1.15, IC1.16, IC1.17, J1.1, J3.2, J4.6, J4.9, J4.14, J4.20, J4.25, J4.30, J4.34, J4.39, J5.2, J6.2, J9.1, J12.1, J16.5, J16.6, J17.3, J19.3, J20.3, J21.3, Q2.3, Q3.3, Q5.3, Q6.3, R1.1, R5.2, R7.2, R8.2, R12.2, R14.1, R21.2, R22.2, R24.2, R26.2, R30.2, R32.2, R34.2, SW1.1, U1.6, U1.18, U1.28, U1.39, U2.10, U2.16, U3.1
HM1: R23.2, U1.13
HM2: R25.2, U1.14
LED1: R19.2, U1.20
LED2: R18.2, U1.21
LED3: R17.2, U1.22
LED4: R16.2, U1.23
M0: U1.36, U2.2
M1: U1.37, U2.3
M2: U1.40, U2.4
MISO: CON1.1, U1.3
MOSI: CON1.4, U1.1
MSWITCH: J8.2, U1.16
unnamed: C1.1, D1.1, Q3.2, R7.1
unnamed: C3.1, IC1.9
unnamed: C5.2, R14.2
unnamed: C6.1, J7.2
unnamed: C7.1, U1.7, Y1.1
unnamed: C8.1, J6.1, U1.8, Y1.2
unnamed: C9.1, U1.29
unnamed: C18.1, U3.7, Y2.1
unnamed: C19.1, U3.8, Y2.2
unnamed: C20.1, U3.4
unnamed: D1.2, R6.1
unnamed: D2.2, R9.1
unnamed: D3.2, R9.2
unnamed: D4.1, D5.2
unnamed: D5.1, R11.1
unnamed: D6.2, R11.2
unnamed: D8.2, R15.1
unnamed: D9.2, R16.1
unnamed: D10.2, R17.1
unnamed: D11.2, R18.1
unnamed: D12.2, R19.1
unnamed: D13.2, R20.2
unnamed: D14.2, J15.2, J17.1, Q5.1, R27.1
unnamed: D15.2, R27.2
unnamed: D16.2, R28.2
unnamed: D17.2, J17.2, J18.2, Q6.1, R28.1
unnamed: D18.2, J16.1
unnamed: IC1.1, IC1.2, IC1.3, L1.1
unnamed: IC1.4, R10.2
unnamed: J1.2, Q1.1
unnamed: J2.1, Q2.2, Q3.1, R4.1, R5.1
unnamed: J2.2, R3.2
unnamed: J8.1, R15.2
unnamed: J10.1, U1.24
unnamed: J10.2, U1.25
unnamed: J10.3, U1.26
unnamed: J11.1, U1.33
unnamed: J11.2, U1.34
unnamed: J13.1, U2.11
unnamed: J13.2, U2.12
unnamed: J14.1, U2.13
unnamed: J14.2, U2.14
unnamed: J16.2, U3.6
unnamed: J16.3, U3.5
unnamed: J19.2, R29.1
unnamed: J20.2, R31.1
unnamed: J21.2, R33.1
unnamed: Q1.2, R1.2
unnamed: Q1.3, Q4.3, R2.1, R3.1
unnamed: Q2.1, Q4.2, R2.2
unnamed: Q5.2, R23.1, R24.1
unnamed: Q6.2, R25.1, R26.1
RESET_M: U1.41, U2.5
RST: C5.1, CON1.5, D7.2, J7.1, R13.2, SW1.2, U1.4
RxD_USB: R35.2, U1.10, U3.3
S1: C15.1, R29.2, R30.1, U1.32
S2: C16.1, R31.2, R32.1, U1.31
S3: C17.1, R33.2, R34.1, U1.30
SCK: CON1.3, U1.2
SLEEP: U1.42, U2.6
STEP: U1.43, U2.7
TxD_USB: U1.9, U3.2
UNLATCH: R6.2, R22.1, U1.19
